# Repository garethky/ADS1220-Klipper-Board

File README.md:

# ADS1220-Klipper-Board
A board for connecting up to 4 Load cells to an ADS1220

## Project Goals
This board is intended to be a reference design for eventual commercial boards that want to implement load cell probing.
We intend to tackle the following problems found with simple prototyping boards that connect via SPI I/O pins:

* Produce a clean 5V power supply on board for low noise load cell bridge measurements
* Reject common 3D printer electrical noise sources including: Voltage Regulators, Steppers, Heaters & 50Hz/60Hz line noise
* Gracefully handle Voltage Spikes & Ground Loops
* Provide Amplification/Gain to support low sensitivity (1mV/V) load cells to be able to measure 1g of force change
* Ability to connect up to 4 load cells in parallel to measure force on a printer's bed

Eventually we would like individuals to be able to order a board from a board house, once we nail down the component selection.

## Project Status: Prototyping
This is currently in the prototyping stage. Prototype goals are as follows:

1. Get it to work!
1. Prototype and test one 5V supply architecture (12V -> 5V via low noise switching regulator)
2. Test 5V to 3.3V via LDO
3. Test with and without 1 differential amplifier. 
4. Investigate voltage spikes and ground loops.

Future prototypes will refine the board:
1. Investigate additional 5V suppy architectures
2. Investigate additional amplifiers
2. Design for Supply Chain an Manufacturability: investigate component alternatives that are asier to get in the CN component supply chain.

## Specs
* ADC: [Texas Instruments ADS1220](https://www.ti.com/product/ADS1220)
* Additional differential amplifier: TK (prototype will try the [Microchip MCP6V92](https://www.microchip.com/en-us/product/mcp6v92) )
* * 4 x 4 pin JST HX connectors for full bridge load cells
* MCU: STMicro [STM32F103C8T](https://www.st.com/en/microcontrollers-microprocessors/stm32f103c8.html) MCU, Arm® Cortex® Cortex M4 @ 75Mhz
  * Klipper and Katapult support this chip well, including flashing over CAN if we decide to enable that later
* USB C for communicating with a klipper host
* Physical Boot and Reset buttons

## Why the ADS1220?
Several printers have shipped with the HX711 ADC chip which only supports 80 samples per second (SPS).
We consider this to be too slow for use as a Probe in the 3D printer as probing speed is limited to ~2mm/s.
There is a faster variant, the HX717, that supports 320 SPS. This shipped in all of Prusa's Nextuder products
and those support probing at up to 10mm/s. We consider this the minimum sample rate required for a 3D printer.

Both of these chips have the disadvantage of not being standard SPI devices and requiring a lot of MCU overhead to support communication.
Their data sheets are also lacking a lot of detail and the HX717 datasheet isnt available in English.

The ADS1220 is a good match for the capabilities of the HX717. Specifically:
* It supports faster sample rates close to 320SPS: 330, 350, 600, 660, 1000 & 1200. Higher sample rates improve the safety margin for
probing if the noise can be kept low and the sensitivity is high. Other ADC chips tend to have a large gap in the sample rate range from 
around 300SPS to 1000SPS.
* It has a PGA that supports up to a gain setting of 128
* Supports standard SPI
* TI provides a detailed datasheet and have reference designs
* Relatively cheap and widely available in the supply chain. Cost is a large
factor in getting a part into a commercial 3D printer board.

Features lacking on the ADS1220:
* The SPI speed is slow
* It lacks a "power reset" register. Reboots due to voltage spikes cant be detected at runtime.
The HX711 & HX717 also lack this feature. Higher end TI product do have this e.g. ADS1263. If we were
shipping a commercial product we would insist on this safety feature.

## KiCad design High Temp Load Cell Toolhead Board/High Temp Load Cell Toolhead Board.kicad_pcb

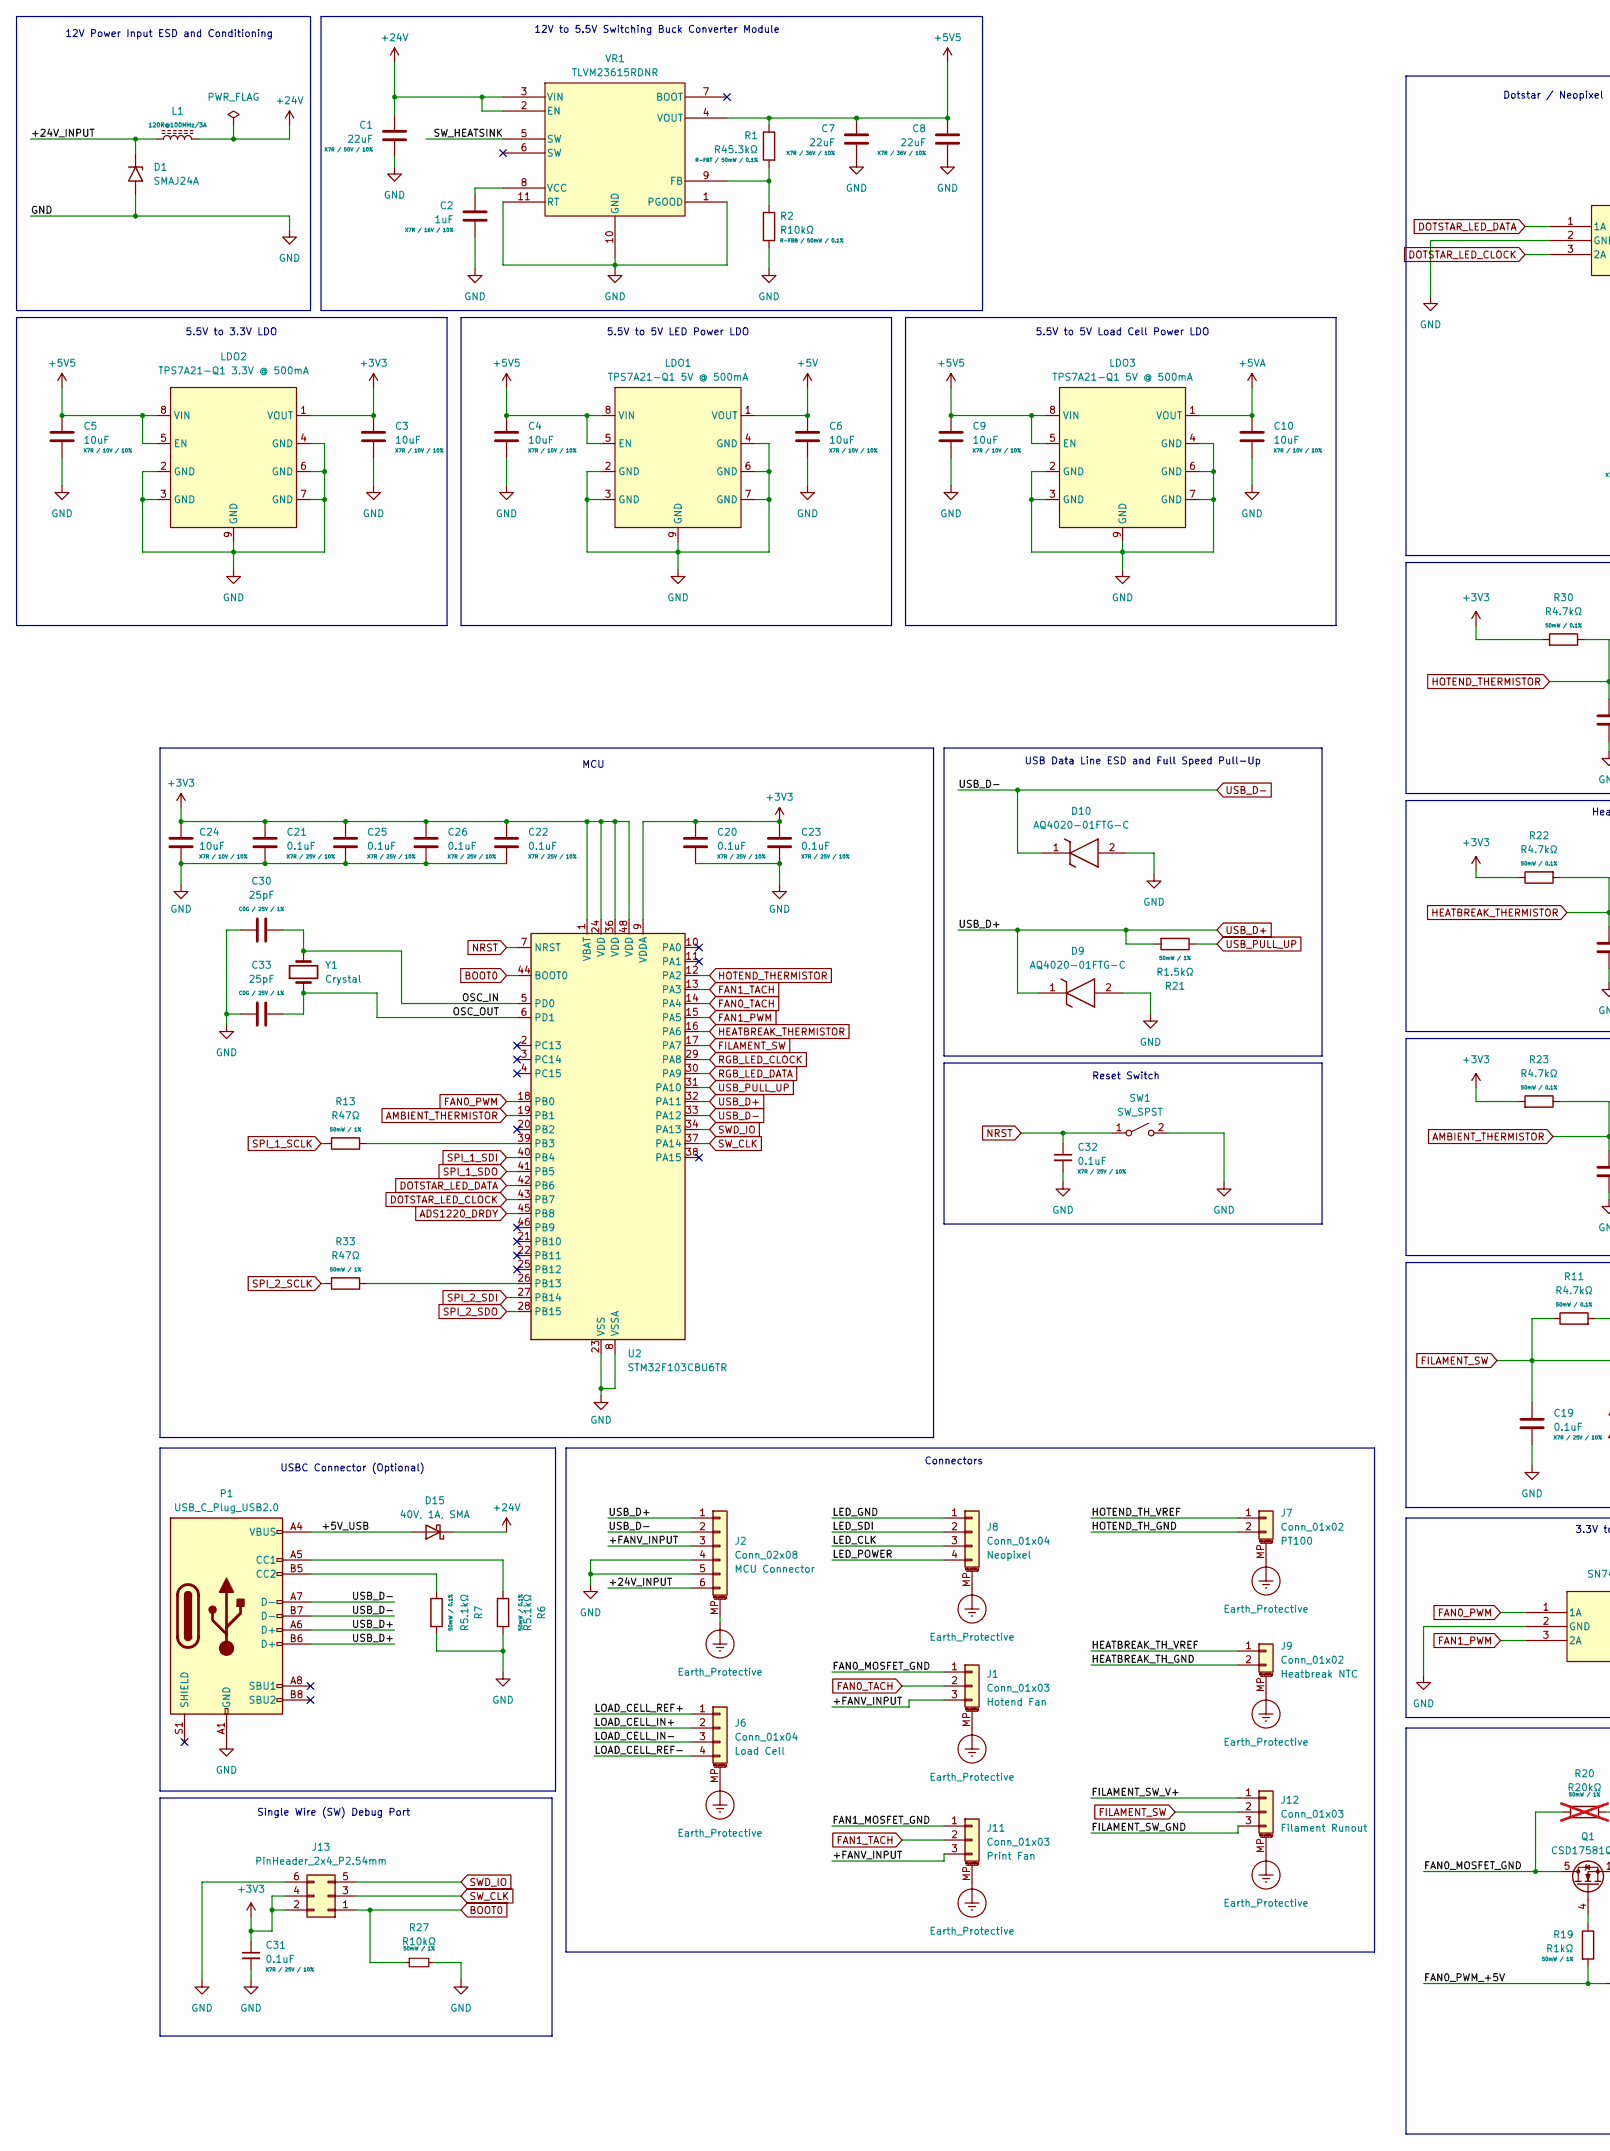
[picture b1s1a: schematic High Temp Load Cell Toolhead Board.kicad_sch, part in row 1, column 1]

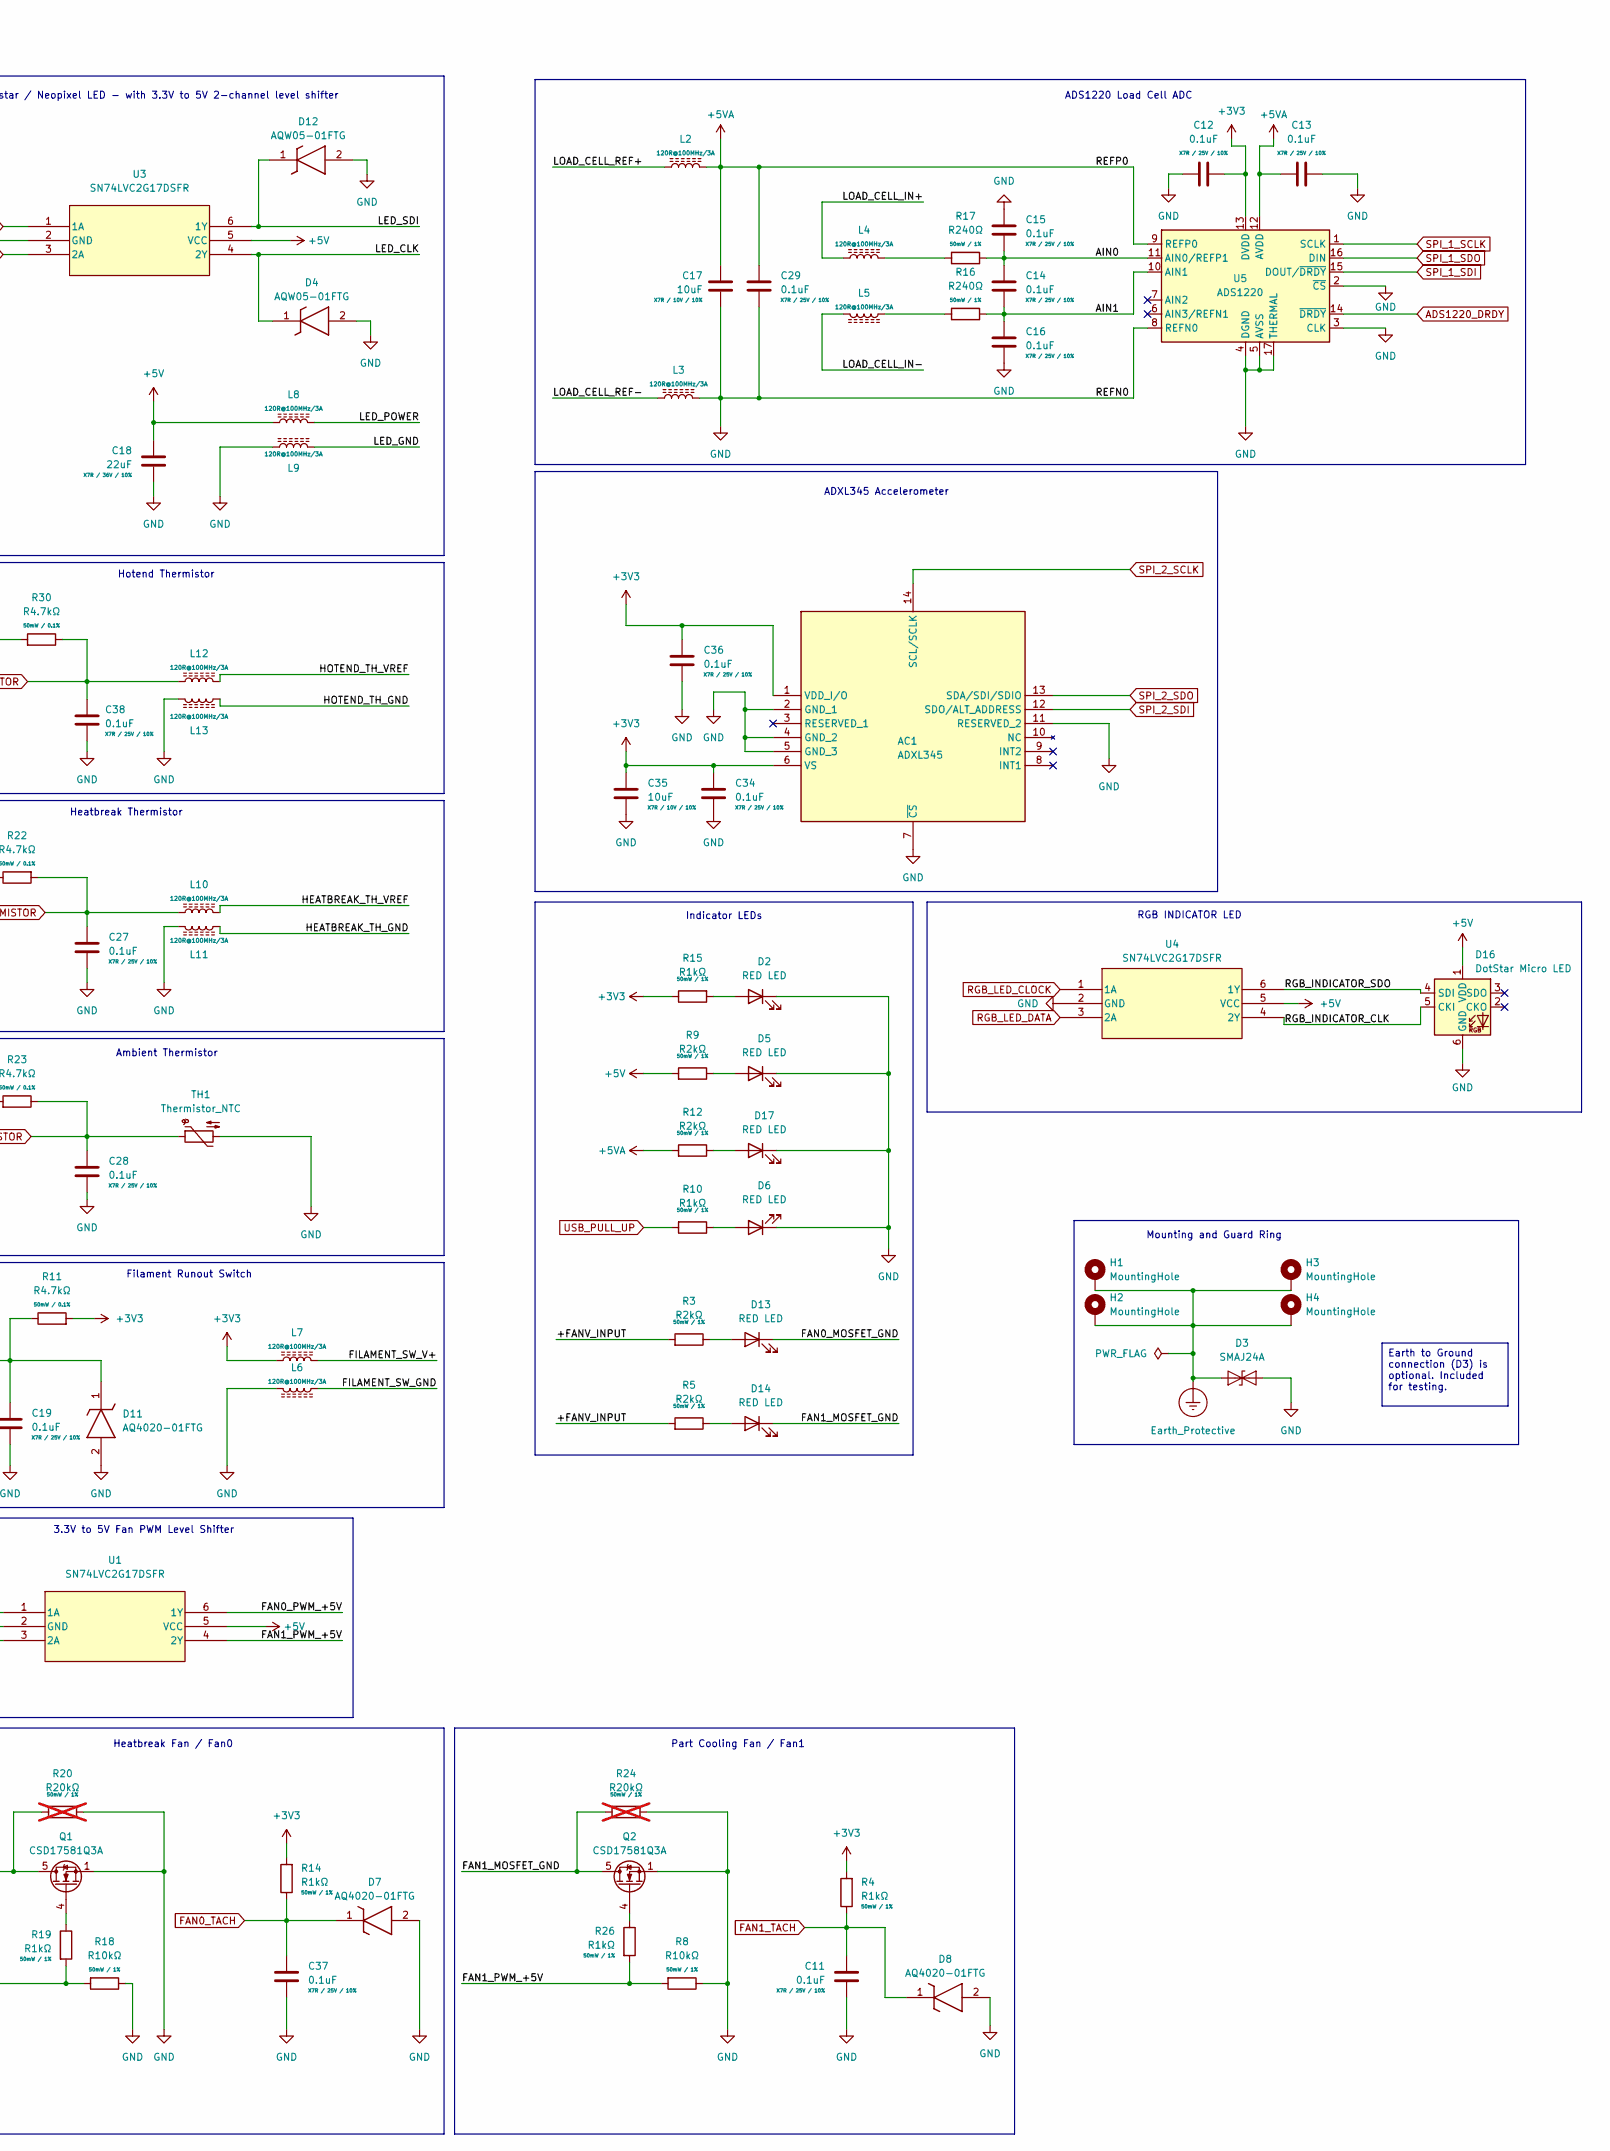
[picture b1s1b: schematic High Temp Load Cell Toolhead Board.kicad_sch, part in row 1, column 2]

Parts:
AC1: ADXL345; Mouser Part Number N/A
C1, C7, C8, C18: 22uF; C_1206_3216Metric
C2: 1uF; C_0805_2012Metric
C3, C4, C5, C6, C9, C10, C17, C24, C35: 10uF; C_1206_3216Metric
C11, C12, C13, C14, C15, C16, C19, C20, C21, C22, C23, C25, C26, C27, C28, C29, C31, C32, C34, C36, C37, C38: 0.1uF; C_0603_1608Metric
C30, C33: 25pF; C_0603_1608Metric
D1, D3: SMAJ24A; D_SMA; Manufacturer_Part_Number SMAJ6A
D2, D5, D13, D14, D17: RED LED; LED_0603_1608Metric; Manufacturer_Part_Number LTST-C193KRKT-5A
D4, D12: AQW05-01FTG; SOD2613X114N; Manufacturer_Part_Number AQW05-01FTG
D6: RED LED; LED_0603_1608Metric; Part Number LTST-C193KRKT-5A
D7, D8, D11: AQ4020-01FTG; SOD2613X114N; Manufacturer_Part_Number AQ4020-01FTG; Mouser Part Number 576-AQ4020-01FTG
D9, D10: AQ4020-01FTG-C; SOD2613X114N; Manufacturer_Part_Number AQ4020-01FTG-C
D15: 40V, 1A, SMA; D_SMA; Manufacturer_Part_Number B140-13-F
D16: DotStar Micro LED; LED-APA102-2020; Part Number APA102-2020
H1, H2, H3, H4: MountingHole; MountingHole_3.2mm_M3_Pad_Via
J1, J11, J12: Conn_01x03; Molex_CLIK-Mate_505405-0370_1x03-1MP_P1.50mm_Vertical; Manufacturer_Part_Number 2132250370
J2: Conn_02x08; Molex_CLIK-Mate_213226-0610_1x06-1MP_P1.50mm_Horizontal; Manufacturer_Part_Number 2132271210
J6: Conn_01x04; Molex_CLIK-Mate_505405-0470_1x04-1MP_P1.50mm_Vertical; Manufacturer_Part_Number 2132250470
J7, J9: Conn_01x02; Molex_CLIK-Mate_505405-0270_1x02-1MP_P1.50mm_Vertical; Manufacturer_Part_Number 2132250230
J8: Conn_01x04; Molex_CLIK-Mate_505405-0470_1x04-1MP_P1.50mm_Vertical; Manufacturer_Part_Number 2132250370
J13: PinHeader_2x4_P2.54mm; PinHeader_2x03_P2.54mm_Vertical
L1, L2, L3, L4, L5, L6, L7, L8, L9, L10, L11, L12, L13: 120R@100MHz/3A; L_0805_2012Metric
LDO1, LDO3: TPS7A21-Q1 5V @ 500mA; VSON-8-1EP_3x3mm_P0.65mm_EP1.65x2.4mm_ThermalVias; Manufacturer_Part_Number TPS7A2150PQWDRBRQ1
LDO2: TPS7A21-Q1 3.3V @ 500mA; VSON-8-1EP_3x3mm_P0.65mm_EP1.65x2.4mm_ThermalVias; Manufacturer_Part_Number TPS7A2133PQWDRBRQ1
P1: USB_C_Plug_USB2.0; USB4145030170C; Manufacturer_Part_Number USB4145-03-0170-C
Q1, Q2: CSD17581Q3A; VSON-8_3.3x3.3mm_P0.65mm_NexFET; Manufacturer_Part_Number CSD17581Q3A
R1: R45.3kΩ; R_0603_1608Metric
R2, R8, R18, R27: R10kΩ; R_0603_1608Metric
R3, R5, R9, R12: R2kΩ; R_0603_1608Metric
R4, R10, R14, R15, R19, R26: R1kΩ; R_0603_1608Metric
R6, R7: R5.1kΩ; R_0603_1608Metric
R11, R22, R23, R30: R4.7kΩ; R_0603_1608Metric
R13, R33: R47Ω; R_0603_1608Metric
R16, R17: R240Ω; R_0603_1608Metric
R20, R24: R20kΩ; R_0603_1608Metric; not fitted
R21: R1.5kΩ; R_0603_1608Metric
SW1: SW_SPST; SW_SPST_PTS810; Manufacturer_Part_Number PTS810SJS250SMTR LFS
TH1: Thermistor_NTC; R_0603_1608Metric; Manufacturer_Part_Number SDNT1608X104F3950FTF
U1, U3, U4: SN74LVC2G17DSFR; SOT-363_SC-70-6; Mouser Part Number 771-LVC1G17GV125; LCSC C6076
U2: STM32F103CBU6TR; QFN-48-1EP_7x7mm_P0.5mm_EP5.6x5.6mm; Manufacturer_Part_Number STM32F103CBU6TR
U5: ADS1220; Texas_RSA_VQFN-16-1EP_4x4mm_P0.65mm_EP2.7x2.7mm; Manufacturer_Part_Number ADS1220IRVAR
VR1: TLVM23615RDNR; CONV_TLVM23615RDNR; Manufacturer_Part_Number TPSM861252RDXR
Y1: Crystal; XTAL_ECS-.327-6-34QCS-TR; Manufacturer_Part_Number ECS-.327-6-34QCS-TR

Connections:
+3V3: AC1.1 (VDD_I/O), AC1.6 (VS), C3.1, C12.2, C20.2, C21.2, C22.2, C23.2, C24.2, C25.2, C26.2, C31.1, C34.1, C35.1, C36.1, J13.2, J13.4, L7.1, LDO2.1 (VOUT), R4.2, R11.2, R14.2, R15.1, R22.1, R23.2, R30.2, U2.1 (VBAT), U2.9 (VDDA), U2.24 (VDD), U2.36 (VDD), U2.48 (VDD), U5.13 (DVDD)
+5V: C6.1, C18.1, D16.1 (VDD), L8.1, LDO1.1 (VOUT), R9.2, U1.5 (VCC), U3.5 (VCC), U4.5 (VCC)
+5V5: C4.1, C5.1, C7.1, C8.1, C9.1, LDO1.5 (EN), LDO1.8 (VIN), LDO2.5 (EN), LDO2.8 (VIN), LDO3.5 (EN), LDO3.8 (VIN), R1.1, VR1.4 (VOUT)
+5VA: C10.1, C13.2, C17.1, C29.1, L2.2, LDO3.1 (VOUT), R12.2, U5.9 (REFP0), U5.12 (AVDD)
+24V: C1.1, D15.1 (K), L1.2, VR1.2 (EN), VR1.3 (VIN)
/+5V_USB: D15.2 (A), P1.A4 (VBUS), P1.A9 (VBUS), P1.B4 (VBUS), P1.B9 (VBUS)
/+24V_INPUT: D1.1 (A1), J2.6, L1.1
/+FANV_INPUT: J1.3, J2.3, J11.3, R3.2, R5.2
/AIN0: C14.1, C15.2, R17.1, U5.11 (AIN0/REFP1)
/AIN1: C14.2, C16.1, R16.1, U5.10 (AIN1)
/FAN0_MOSFET_GND: D13.1 (K), J1.1, Q1.5 (D), R20.2
/FAN0_PWM_+5V: R18.2, R19.2, U1.6 (1Y)
/FAN1_MOSFET_GND: D14.1 (K), J11.1, Q2.5 (D), R24.2
/FAN1_PWM_+5V: R8.2, R26.2, U1.4 (2Y)
/FILAMENT_SW_GND: J12.3, L6.1
/FILAMENT_SW_V+: J12.1, L7.2
/HEATBREAK_TH_GND: J9.2, L11.1
/HEATBREAK_TH_VREF: J9.1, L10.1
/HOTEND_TH_GND: J7.2, L13.1
/HOTEND_TH_VREF: J7.1, L12.2
/LED_CLK: D4.1 (K), J8.3, U3.4 (2Y)
/LED_GND: J8.1, L9.1
/LED_POWER: J8.4, L8.2
/LED_SDI: D12.1 (K), J8.2, U3.6 (1Y)
/LOAD_CELL_IN+: J6.2, L4.1
/LOAD_CELL_IN-: J6.3, L5.2
/LOAD_CELL_REF+: J6.1, L2.1
/LOAD_CELL_REF-: J6.4, L3.1
/OSC_IN: C30.2, U2.5 (PD0), Y1.2
/OSC_OUT: C33.2, U2.6 (PD1), Y1.1
/RGB_INDICATOR_CLK: D16.5 (CKI), U4.4 (2Y)
/RGB_INDICATOR_SDO: D16.4 (SDI), U4.6 (1Y)
/SW_HEATSINK: VR1.5 (SW)
ADS1220_DRDY: U2.45 (PB8), U5.14 (~DRDY)
AMBIENT_THERMISTOR: C28.1, R23.1, TH1.1, U2.19 (PB1)
BOOT0: J13.1, R27.1, U2.44 (BOOT0)
DOTSTAR_LED_CLOCK: U2.43 (PB7), U3.3 (2A)
DOTSTAR_LED_DATA: U2.42 (PB6), U3.1 (1A)
Earth_Protective: D3.1 (A1), H1.1, H2.1, H3.1, H4.1, J1.MP (MountPin), J2.MP (MountPin), J6.MP (MountPin), J7.MP (MountPin), J8.MP (MountPin), J9.MP (MountPin), J11.MP (MountPin), J12.MP (MountPin)
FAN0_PWM: U1.1 (1A), U2.18 (PB0)
FAN0_TACH: C37.1, D7.1 (K), J1.2, R14.1, U2.14 (PA4)
FAN1_PWM: U1.3 (2A), U2.15 (PA5)
FAN1_TACH: C11.1, D8.1 (K), J11.2, R4.1, U2.13 (PA3)
FILAMENT_SW: C19.1, D11.1 (K), J12.2, R11.1, U2.17 (PA7)
GND: AC1.2 (GND_1), AC1.4 (GND_2), AC1.5 (GND_3), AC1.7 (~CS), AC1.11 (RESERVED_2), C1.2, C2.2, C3.2, C4.2, C5.2, C6.2, C7.2, C8.2, C9.2, C10.2, C11.2, C12.1, C13.1, C15.1, C16.2, C17.2, C18.2, C19.2, C20.1, C21.1, C22.1, C23.1, C24.1, C25.1, C26.1, C27.2, C28.2, C29.2, C30.1, C31.2, C32.2, C33.1, C34.2, C35.2, C36.2, C37.2, C38.2, D1.2 (A2), D2.1 (K), D3.2 (A2), D4.2 (A), D5.1 (K), D6.1 (K), D7.2 (A), D8.2 (A), D9.2 (A), D10.2 (A), D11.2 (A), D12.2 (A), D16.6 (GND), D17.1 (K), J2.4, J2.5, J13.6, L3.2, L6.2, L9.2, L11.2, L13.2, LDO1.2 (GND), LDO1.3 (GND), LDO1.4 (GND), LDO1.6 (GND), LDO1.7 (GND), LDO1.9 (GND), LDO2.2 (GND), LDO2.3 (GND), LDO2.4 (GND), LDO2.6 (GND), LDO2.7 (GND), LDO2.9 (GND), LDO3.2 (GND), LDO3.3 (GND), LDO3.4 (GND), LDO3.6 (GND), LDO3.7 (GND), LDO3.9 (GND), P1.A1 (GND), P1.A12 (GND), P1.B1 (GND), P1.B12 (GND), Q1.1 (S), Q1.2 (S), Q1.3 (S), Q2.1 (S), Q2.2 (S), Q2.3 (S), R2.2, R6.2, R7.2, R8.1, R18.1, R20.1, R24.1, R27.2, SW1.2 (B), TH1.2, U1.2 (GND), U2.8 (VSSA), U2.23 (VSS), U2.35 (VSS), U2.47 (VSS), U2.49 (VSS), U3.2 (GND), U4.2 (GND), U5.2 (~CS), U5.3 (CLK), U5.4 (DGND), U5.5 (AVSS), U5.8 (REFN0), U5.17 (THERMAL), VR1.1 (PGOOD), VR1.10 (GND), VR1.11 (RT)
HEATBREAK_THERMISTOR: C27.1, L10.2, R22.2, U2.16 (PA6)
HOTEND_THERMISTOR: C38.1, L12.1, R30.1, U2.12 (PA2)
NRST: C32.1, SW1.1 (A), U2.7 (NRST)
unnamed: D2.2 (A), R15.2
unnamed: D5.2 (A), R9.1
unnamed: D6.2 (A), R10.1
unnamed: D13.2 (A), R3.1
unnamed: D14.2 (A), R5.1
unnamed: D17.2 (A), R12.1
unnamed: L4.2, R17.2
unnamed: L5.1, R16.2
unnamed: P1.A5 (CC1), R6.1
unnamed: P1.B5 (CC2), R7.1
unnamed: Q1.4 (G), R19.1
unnamed: Q2.4 (G), R26.1
unnamed: R13.1, U2.39 (PB3)
unnamed: R33.1, U2.26 (PB13)
unnamed: R1.2, R2.1, VR1.9 (FB)
unnamed: C2.1, VR1.8 (VCC)
RGB_LED_CLOCK: U2.29 (PA8), U4.1 (1A)
RGB_LED_DATA: U2.30 (PA9), U4.3 (2A)
SPI_1_SCLK: R13.2, U5.1 (SCLK)
SPI_1_SDI: U2.40 (PB4), U5.15 (DOUT/~DRDY)
SPI_1_SDO: U2.41 (PB5), U5.16 (DIN)
SPI_2_SCLK: AC1.14 (SCL/SCLK), R33.2
SPI_2_SDI: AC1.12 (SDO/ALT_ADDRESS), U2.27 (PB14)
SPI_2_SDO: AC1.13 (SDA/SDI/SDIO), U2.28 (PB15)
SWD_IO: J13.5, U2.34 (PA13)
SW_CLK: J13.3, U2.37 (PA14)
USB_D+: D9.1 (K), J2.1, P1.A6 (D+), P1.B6 (D+), R21.2, U2.32 (PA11)
USB_D-: D10.1 (K), J2.2, P1.A7 (D-), P1.B7 (D-), U2.33 (PA12)
USB_PULL_UP: R10.2, R21.1, U2.31 (PA10)

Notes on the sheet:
Earth to Ground connection (D3) is optional. Included for testing.
5.5V to 5V LED Power LDO
3.3V to 5V Fan PWM Level Shifter
MCU
Heatbreak Thermistor
USB Data Line ESD and Full Speed Pull-Up
Indicator LEDs
ADS1220 Load Cell ADC
5.5V to 3.3V LDO
Hotend Thermistor
Dotstar / Neopixel LED - with 3.3V to 5V 2-channel level shifter
Filament Runout Switch
Heatbreak Fan / Fan0
Ambient Thermistor
12V Power Input ESD and Conditioning
RGB INDICATOR LED
5.5V to 5V Load Cell Power LDO
USBC Connector (Optional)
12V to 5.5V Switching Buck Converter Module
Part Cooling Fan / Fan1
Connectors
Mounting and Guard Ring
Single Wire (SW) Debug Port
ADXL345 Accelerometer
Reset Switch

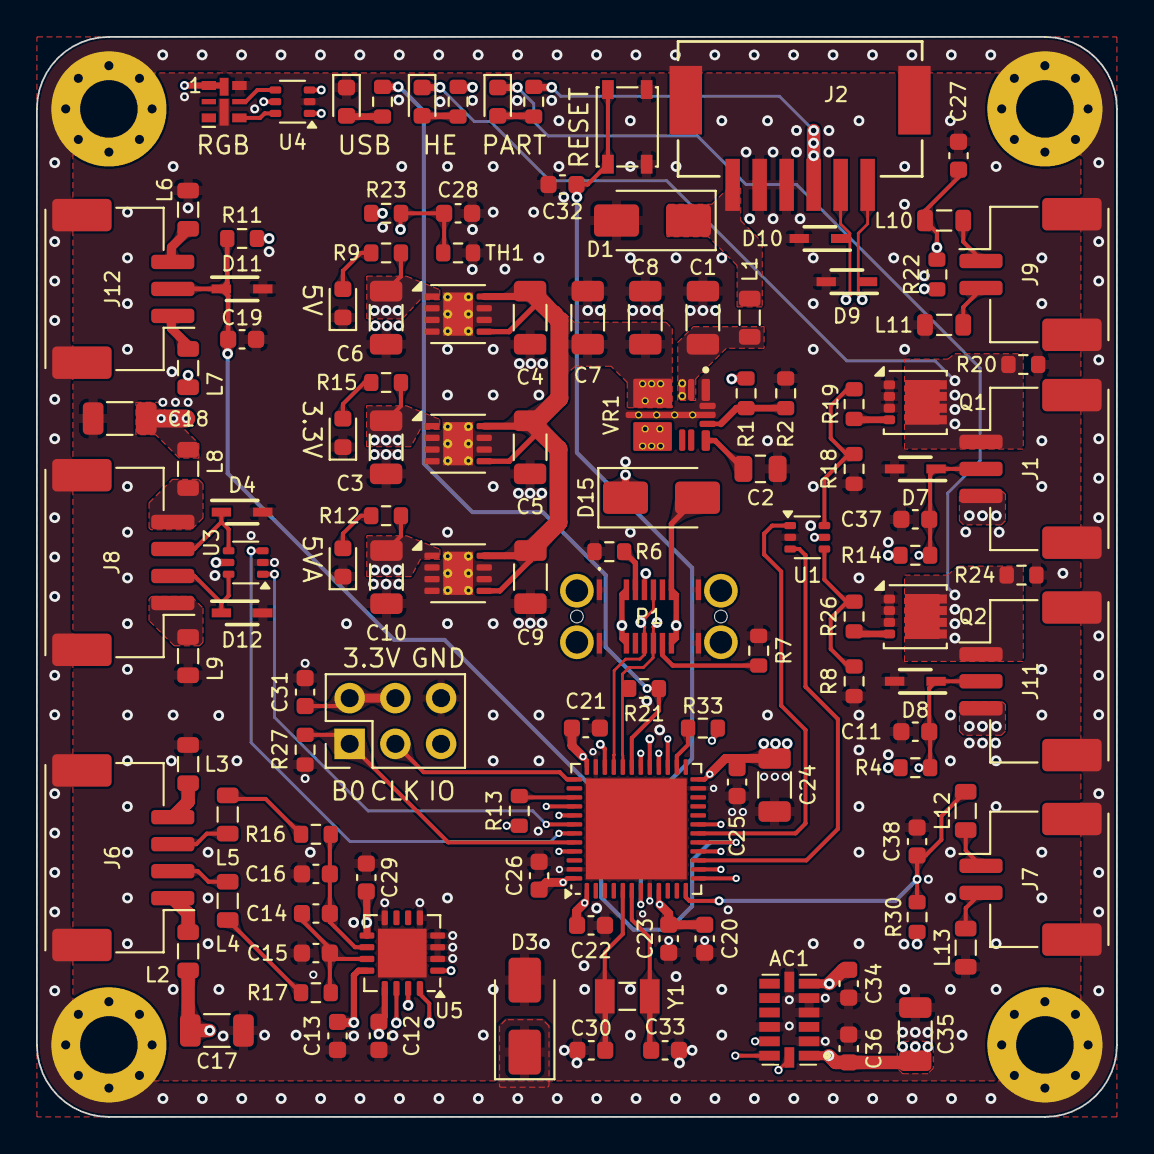
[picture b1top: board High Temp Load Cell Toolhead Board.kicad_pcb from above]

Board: 6 copper layers, 60.0 x 60.0 mm, 125 parts (0 on the bottom side), 76 nets.

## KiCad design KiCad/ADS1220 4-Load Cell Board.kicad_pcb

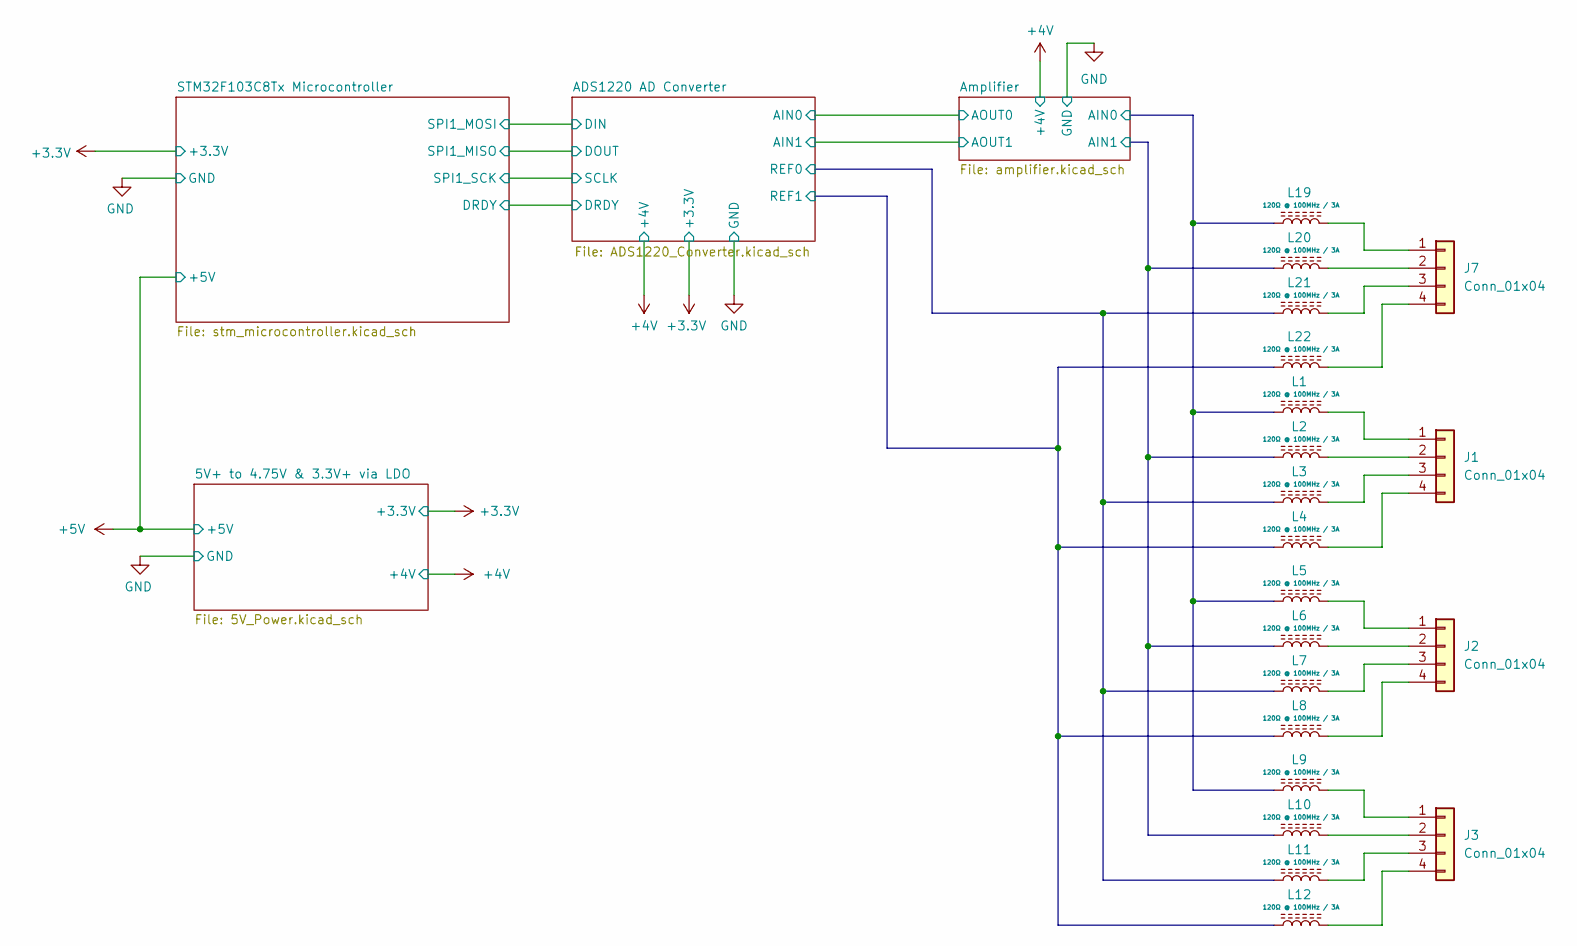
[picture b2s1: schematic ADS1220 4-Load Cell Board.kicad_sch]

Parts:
J1, J2, J3, J7: Conn_01x04; JST_XH_B4B-XH-A_1x04_P2.50mm_Vertical
L1, L2, L3, L4, L5, L6, L7, L8, L9, L10, L11, L12, L19, L20, L21, L22: 120Ω @ 100MHz / 3A; L_0805_2012Metric_Pad1.05x1.20mm_HandSolder

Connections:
/Amplifier/AIN0: L1.1, L5.1, L9.1, L19.1; also elsewhere on the board
/Amplifier/AIN1: L2.1, L6.1, L10.1, L20.1; also elsewhere on the board
unnamed: J1.1, L1.2
unnamed: J1.2, L2.2
unnamed: J1.3, L3.2
unnamed: J1.4, L4.2
unnamed: J2.1, L5.2
unnamed: J2.2, L6.2
unnamed: J2.3, L7.2
unnamed: J2.4, L8.2
unnamed: J3.1, L9.2
unnamed: J3.2, L10.2
unnamed: J3.3, L11.2
unnamed: J3.4, L12.2
unnamed: J7.1, L19.2
unnamed: J7.2, L20.2
unnamed: J7.3, L21.2
unnamed: J7.4, L22.2

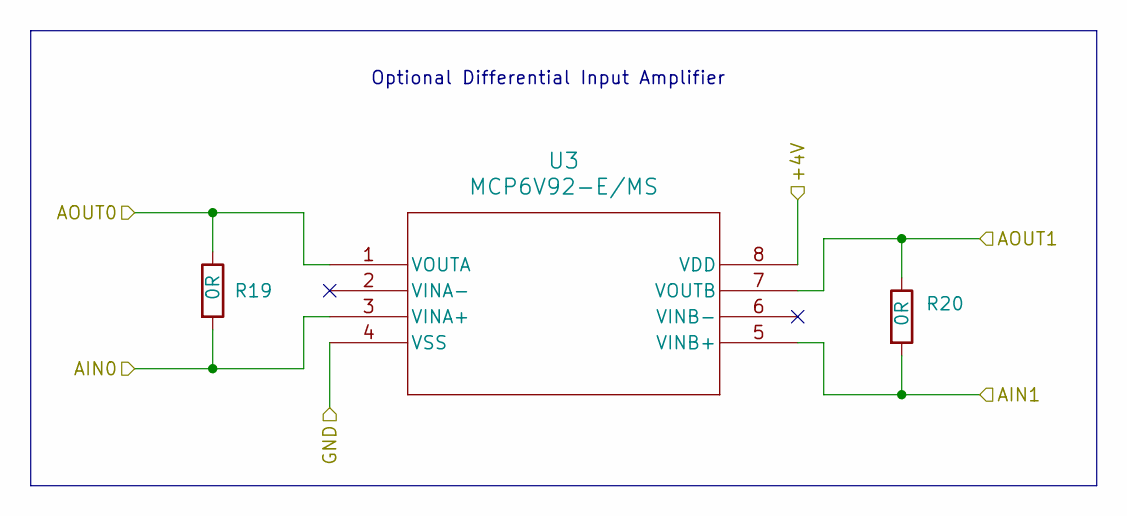
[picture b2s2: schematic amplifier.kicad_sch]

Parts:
R19, R20: 0R; R_0805_2012Metric_Pad1.20x1.40mm_HandSolder
U3: MCP6V92-E/MS; MSOP8_MS_MCH

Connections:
/ADS1220 AD Converter/AIN0: R19.1, U3.1 (VOUTA); also elsewhere on the board
/ADS1220 AD Converter/AIN1: R20.1, U3.7 (VOUTB); also elsewhere on the board
/Amplifier/AIN0: R19.2, U3.3 (VINA+); also elsewhere on the board
/Amplifier/AIN1: R20.2, U3.5 (VINB+); also elsewhere on the board

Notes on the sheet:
Optional Differential Input Amplifier

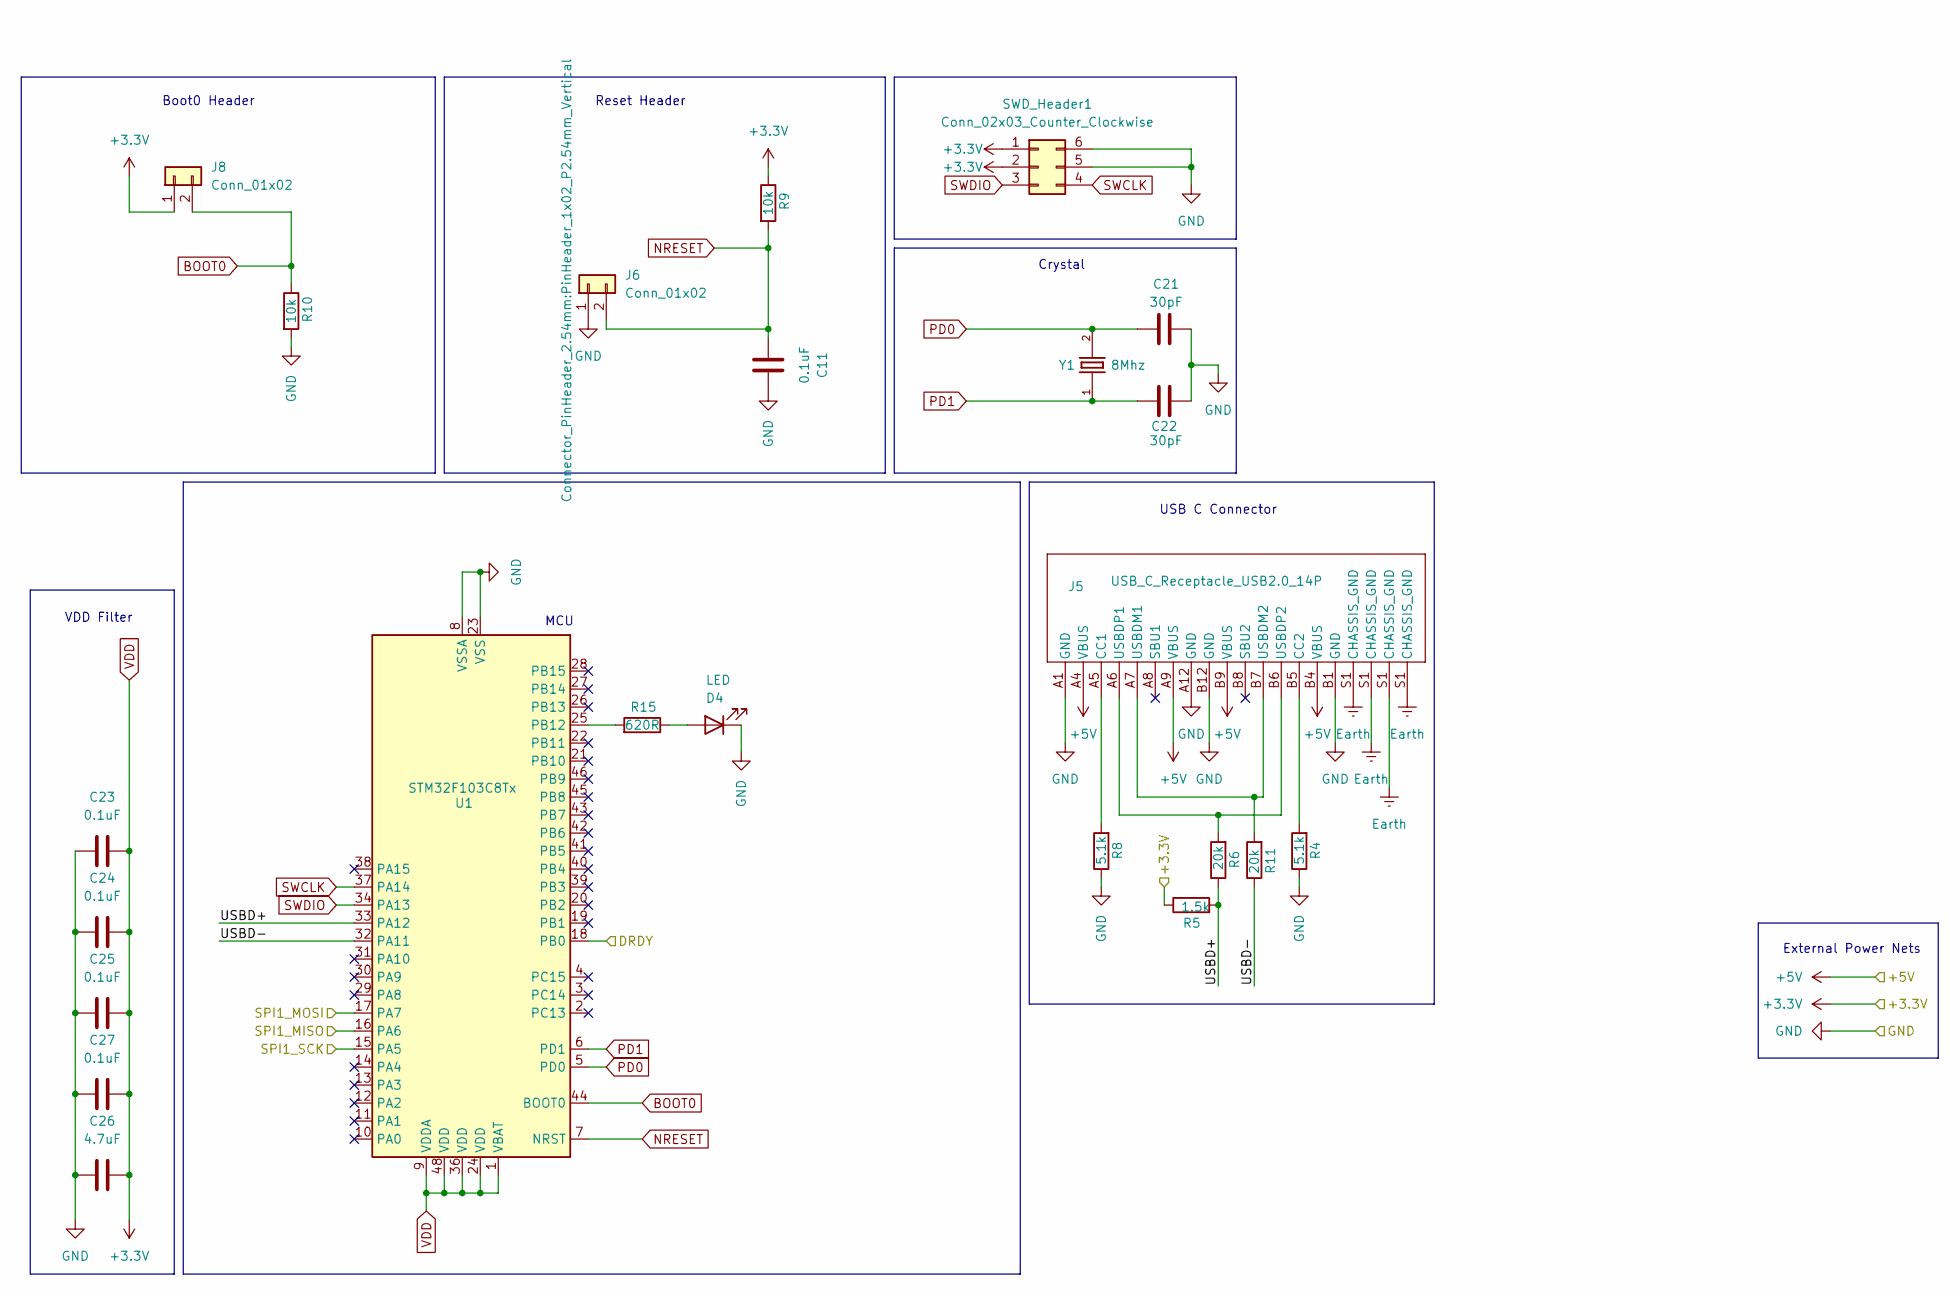
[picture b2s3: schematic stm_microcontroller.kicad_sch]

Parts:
C11, C23, C24, C25, C27: 0.1uF; C_0805_2012Metric_Pad1.18x1.45mm_HandSolder
C21, C22: 30pF; C_0805_2012Metric_Pad1.18x1.45mm_HandSolder
C26: 4.7uF; C_0805_2012Metric_Pad1.18x1.45mm_HandSolder
D4: LED; LED_1206_3216Metric_Pad1.42x1.75mm_HandSolder
J5: USB_C_Receptacle_USB2.0_14P; USB_C_Receptacle_GCT_USB4085
J6, J8: Conn_01x02; PinHeader_1x02_P2.54mm_Vertical
R4, R8: 5.1k; R_0805_2012Metric_Pad1.20x1.40mm_HandSolder
R5: 1.5k; R_0805_2012Metric_Pad1.20x1.40mm_HandSolder
R6, R11: 20k; R_0805_2012Metric_Pad1.20x1.40mm_HandSolder
R9, R10: 10k; R_0805_2012Metric_Pad1.20x1.40mm_HandSolder
R15: 620R; R_0805_2012Metric_Pad1.20x1.40mm_HandSolder
SWD_Header1: Conn_02x03_Counter_Clockwise; PinHeader_2x03_P2.54mm_Vertical
U1: STM32F103C8Tx; LQFP48_STM
Y1: 8Mhz; XTAL_ECS-80-18-30-JGN-TR; PARTREV 2017

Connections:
+5V: J5.A4 (VBUS), J5.A9 (VBUS), J5.B4 (VBUS), J5.B9 (VBUS); also elsewhere on the board
/ADS1220 AD Converter/DIN: U1.17 (PA7); also elsewhere on the board
/ADS1220 AD Converter/DOUT: U1.16 (PA6); also elsewhere on the board
/ADS1220 AD Converter/DRDY: U1.18 (PB0); also elsewhere on the board
/ADS1220 AD Converter/SCLK: U1.15 (PA5); also elsewhere on the board
/STM32F103C8Tx Microcontroller/USBD+: R5.2, R6.1, U1.33 (PA12)
/STM32F103C8Tx Microcontroller/USBD-: R11.1, U1.32 (PA11)
BOOT0: J8.2, R10.1, U1.44 (BOOT0)
Earth: J5.S1 (CHASSIS_GND)
NRESET: C11.1, J6.2, R9.2, U1.7 (NRST)
unnamed: D4.2 (A), R15.1
unnamed: J5.A5 (CC1), R8.2
unnamed: J5.B5 (CC2), R4.2
unnamed: J5.A7 (USBDM1), J5.B7 (USBDM2), R11.2
unnamed: J5.A6 (USBDP1), J5.B6 (USBDP2), R6.2
unnamed: R15.2, U1.25 (PB12)
PD0: C21.1, U1.5 (PD0), Y1.2
PD1: C22.2, U1.6 (PD1), Y1.1
SWCLK: SWD_Header1.4, U1.37 (PA14)
SWDIO: SWD_Header1.3, U1.34 (PA13)

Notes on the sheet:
Reset Header
USB C Connector
Crystal
Boot0 Header
MCU
VDD Filter
External Power Nets

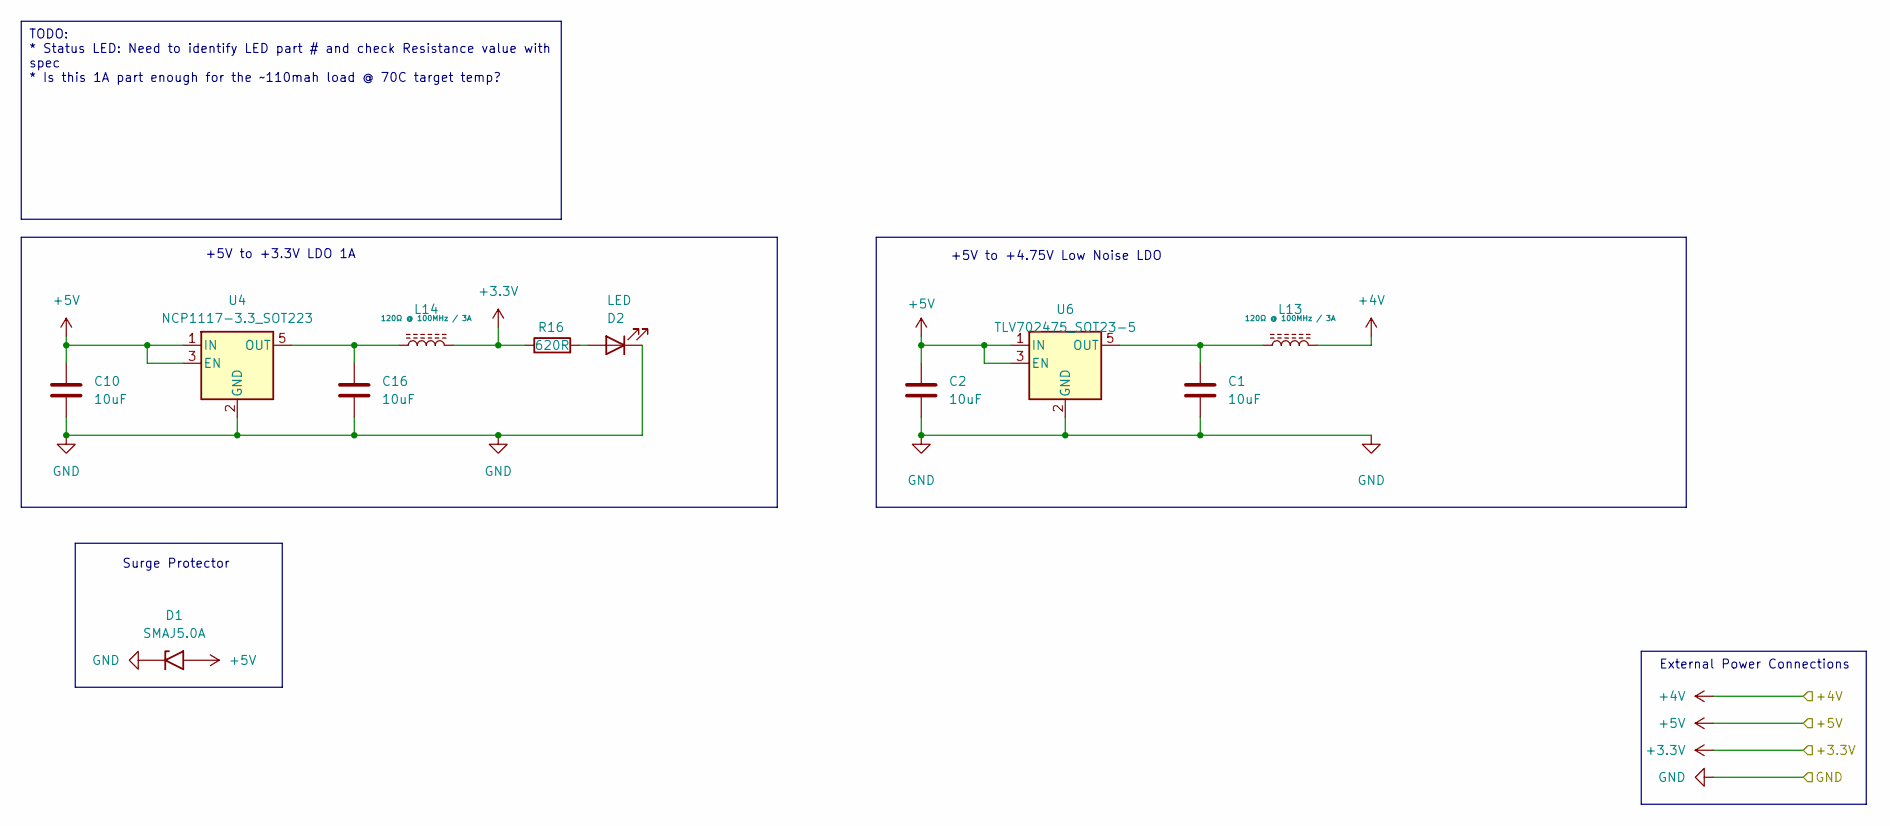
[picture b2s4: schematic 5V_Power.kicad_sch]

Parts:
C1, C2, C10, C16: 10uF; C_0805_2012Metric_Pad1.18x1.45mm_HandSolder
D1: SMAJ5.0A; D_SMA
D2: LED; LED_1206_3216Metric_Pad1.42x1.75mm_HandSolder
L13, L14: 120Ω @ 100MHz / 3A; L_0805_2012Metric_Pad1.05x1.20mm_HandSolder
R16: 620R; R_0805_2012Metric_Pad1.20x1.40mm_HandSolder
U4: NCP1117-3.3_SOT223; SOT-23-5
U6: TLV702475_SOT23-5; SOT-23-5_HandSoldering

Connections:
+5V: C2.1, C10.1, D1.2 (A2), U4.1 (IN), U4.3 (EN), U6.1 (IN), U6.3 (EN); also elsewhere on the board
unnamed: D2.2 (A), R16.2
unnamed 37: L13.2; also elsewhere on the board
unnamed 46: C16.1, L14.1, U4.5 (OUT); also elsewhere on the board
unnamed 47: C1.1, L13.1, U6.5 (OUT); also elsewhere on the board

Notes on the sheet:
TODO: * Status LED: Need to identify LED part # and check Resistance value with spec * Is this 1A part enough for the ~110mah load @ 70C target temp?
Surge Protector
External Power Connections
+5V to +3.3V LDO 1A
+5V to +4.75V Low Noise LDO
